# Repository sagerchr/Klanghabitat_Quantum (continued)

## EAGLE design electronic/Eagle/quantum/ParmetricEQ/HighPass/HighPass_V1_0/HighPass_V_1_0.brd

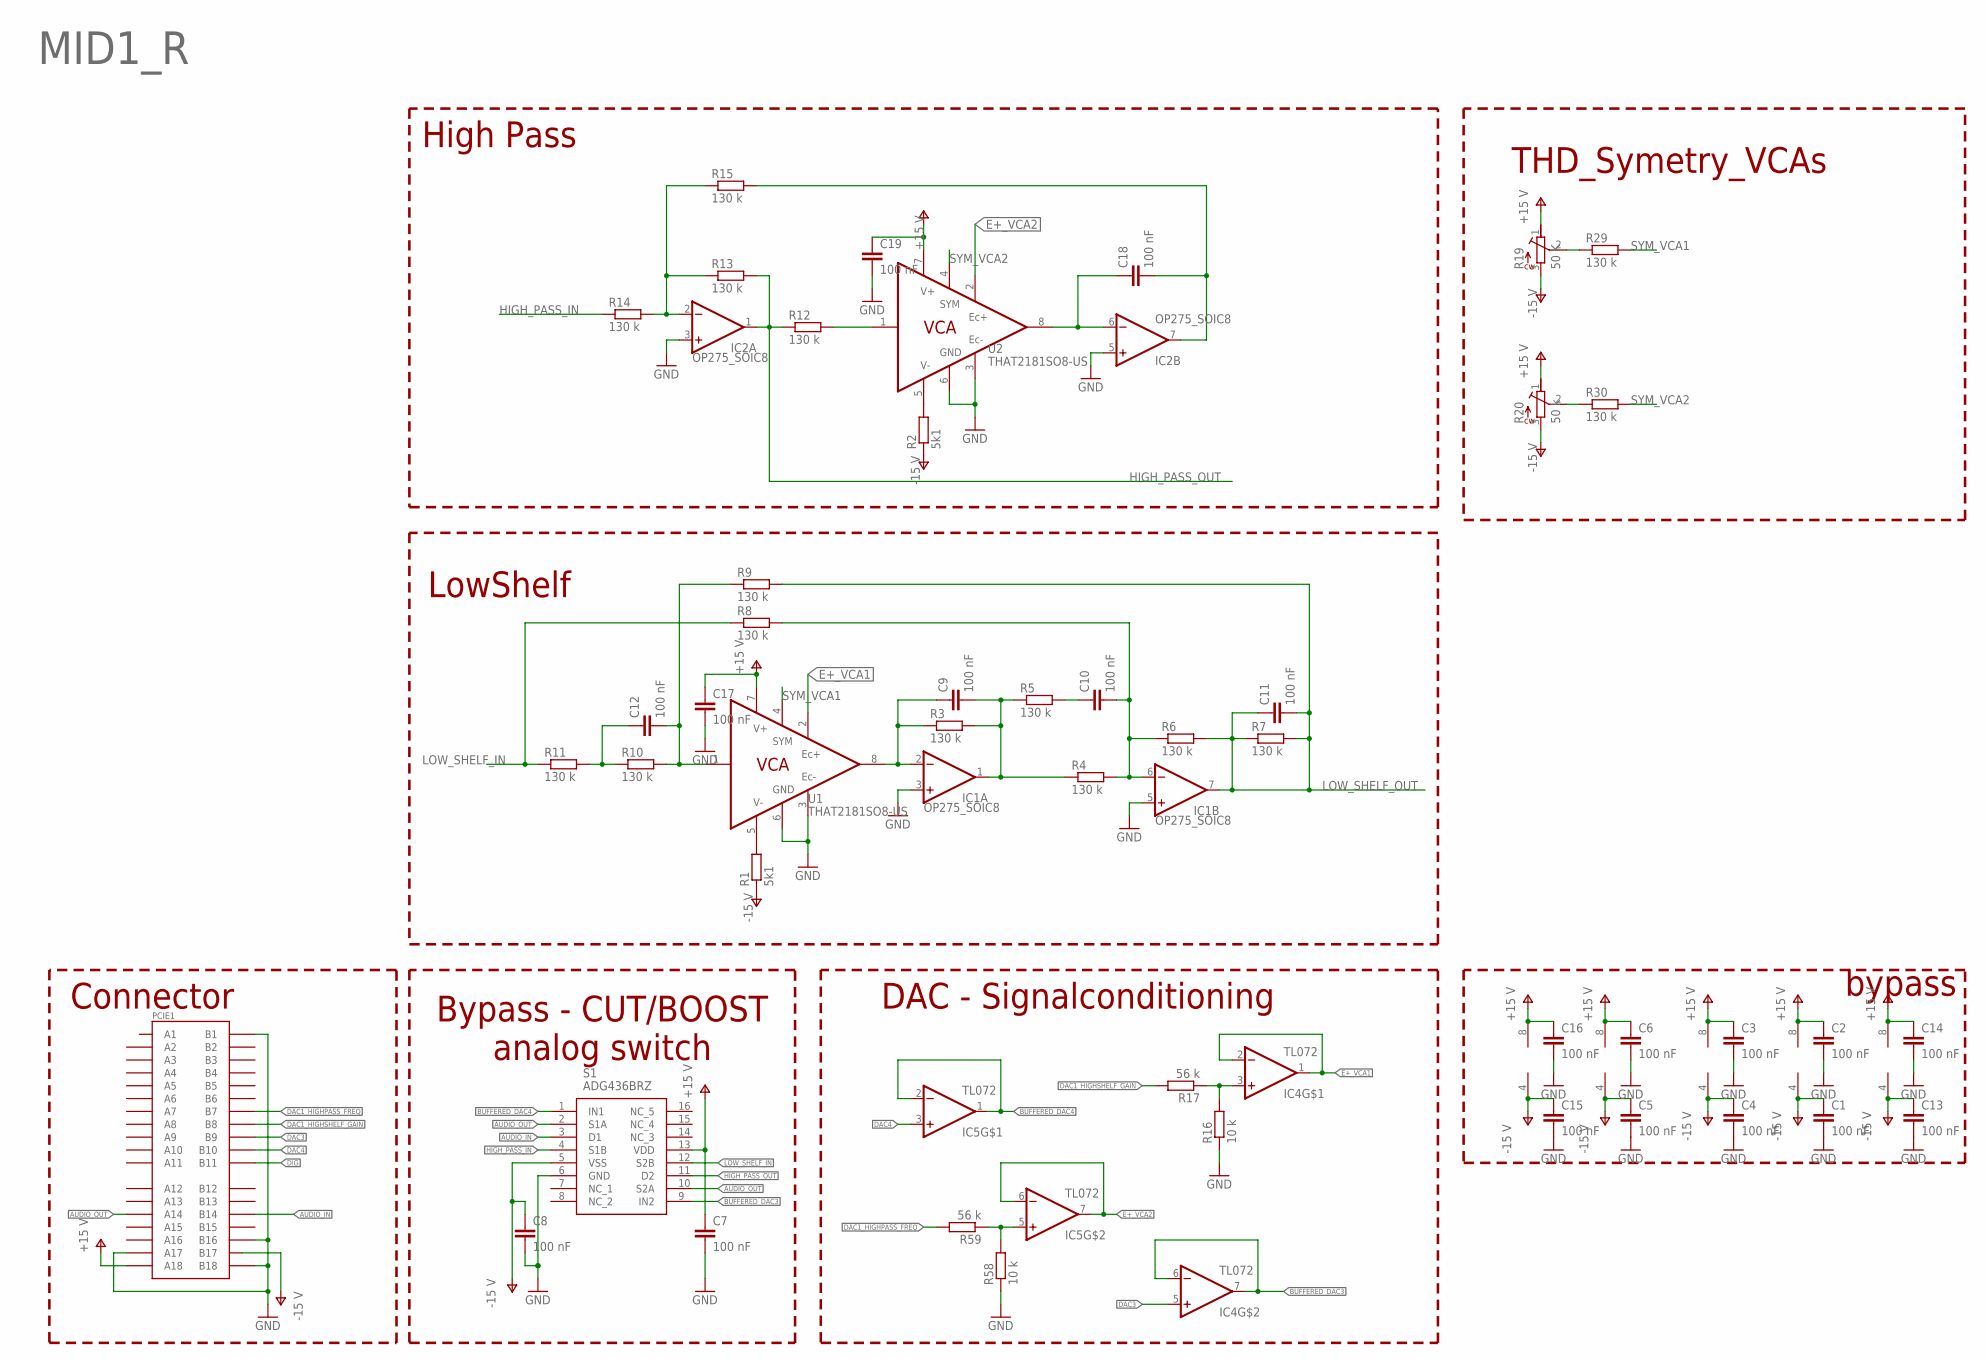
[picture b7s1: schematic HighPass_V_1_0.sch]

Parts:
C1, C2, C3, C4, C5, C6, C7, C8, C9, C10, C11, C12, C13, C14, C15, C16, C17, C18, C19: 100 nF; C0603
IC1, IC2, IC3: OP275_SOIC8; SOIC8
IC4, IC5: TL072; SOIC8
PCIE1: PCIE-36-EDGE
R1, R2: 5k1; R0603
R3, R4, R5, R6, R7, R8, R9, R10, R11, R12, R13, R14, R15, R29, R30: 130 k; R0603
R16, R58: 10 k; R0603
R17, R59: 56 k; R0603
R19: 50 K; TC33X2503G
R20: 50 k; TC33X2503G
S1: ADG436BRZ; SOIC127P600X175-16N
U1, U2: THAT2181SO8-US; SO08

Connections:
AUDIO_IN: PCIE1.B14, S1.3 (D1)
AUDIO_OUT: PCIE1.A14, S1.2 (S1A), S1.10 (S2A)
BUFFERED_DAC3: IC4.6 (-IN), IC4.7 (OUT), S1.9 (IN2)
BUFFERED_DAC4: IC5.1 (OUT), IC5.2 (-IN), S1.1 (IN1)
DAC1_HIGHPASS_FREQ: PCIE1.B7, R59.2
DAC1_HIGHSHELF_GAIN: PCIE1.B8, R17.2
DAC3: IC4.5 (+IN), PCIE1.B9
DAC4: IC5.3 (+IN), PCIE1.B10
DIG: PCIE1.B11
E+_VCA1: IC4.1 (OUT), IC4.2 (-IN), U1.2 (EC+)
E+_VCA2: IC5.6 (-IN), IC5.7 (OUT), U2.2 (EC+)
GND: C1.2, C2.2, C3.2, C4.2, C5.2, C6.2, C7.2, C8.2, C13.2, C14.2, C15.2, C16.2, C17.2, C19.2, IC1.3 (+IN), IC1.5 (+IN), IC2.3 (+IN), IC2.5 (+IN), PCIE1.A17, PCIE1.B1, PCIE1.B16, PCIE1.B18, R16.1, R58.1, S1.6 (GND), U1.3 (EC-), U1.6 (GND), U2.3 (EC-), U2.6 (GND)
HIGH_PASS_IN: R14.1, S1.4 (S1B)
HIGH_PASS_OUT: IC2.1 (OUT), R12.1, R13.2, S1.11 (D2)
LOW_SHELF_IN: R8.1, R11.1, S1.12 (S2B)
LOW_SHELF_OUT: C11.1, C11.2, IC1.7 (OUT), R6.2, R7.1, R7.2, R9.2
unnamed: R1.2, U1.5 (V-)
unnamed: R2.2, U2.5 (V-)
unnamed: C9.1, IC1.2 (-IN), R3.1, U1.8 (OUT)
unnamed: C10.2, IC1.6 (-IN), R4.2, R6.1, R8.2
unnamed: C9.2, IC1.1 (OUT), R3.2, R4.1, R5.1
unnamed: C10.1, R5.2
unnamed: R12.2, U2.1 (IN)
unnamed: C12.2, R9.1, R10.2, U1.1 (IN)
unnamed: IC4.3 (+IN), R16.2, R17.1
unnamed: C12.1, R10.1, R11.2
unnamed: IC2.2 (-IN), R13.1, R14.2, R15.1
unnamed: C18.2, IC2.7 (OUT), R15.2
unnamed: C18.1, IC2.6 (-IN), U2.8 (OUT)
unnamed: R19.2, R29.1
unnamed: R20.2, R30.1
unnamed: IC5.5 (+IN), R58.2, R59.1
SYM_VCA1: R29.2, U1.4 (SYM)
SYM_VCA2: R30.2, U2.4 (SYM)
V+: C2.1, C3.1, C6.1, C7.1, C14.1, C16.1, C17.1, C19.1, IC1.8 (V+), IC2.8 (V+), IC3.8 (V+), IC4.8 (V+), IC5.8 (V+), PCIE1.A18, R19.1 (3), R20.1 (3), S1.13 (VDD), U1.7 (V+), U2.7 (V+)
V-: C1.1, C4.1, C5.1, C8.1, C13.1, C15.1, IC1.4 (V-), IC2.4 (V-), IC3.4 (V-), IC4.4 (V-), IC5.4 (V-), PCIE1.B17, R1.1, R2.1, R19.3 (1), R20.3 (1), S1.5 (VSS)

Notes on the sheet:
DAC - Signalconditioning
MID1_R
LowShelf
High Pass
bypass
Bypass - CUT/BOOST analog switch
THD_Symetry_VCAs
Connector

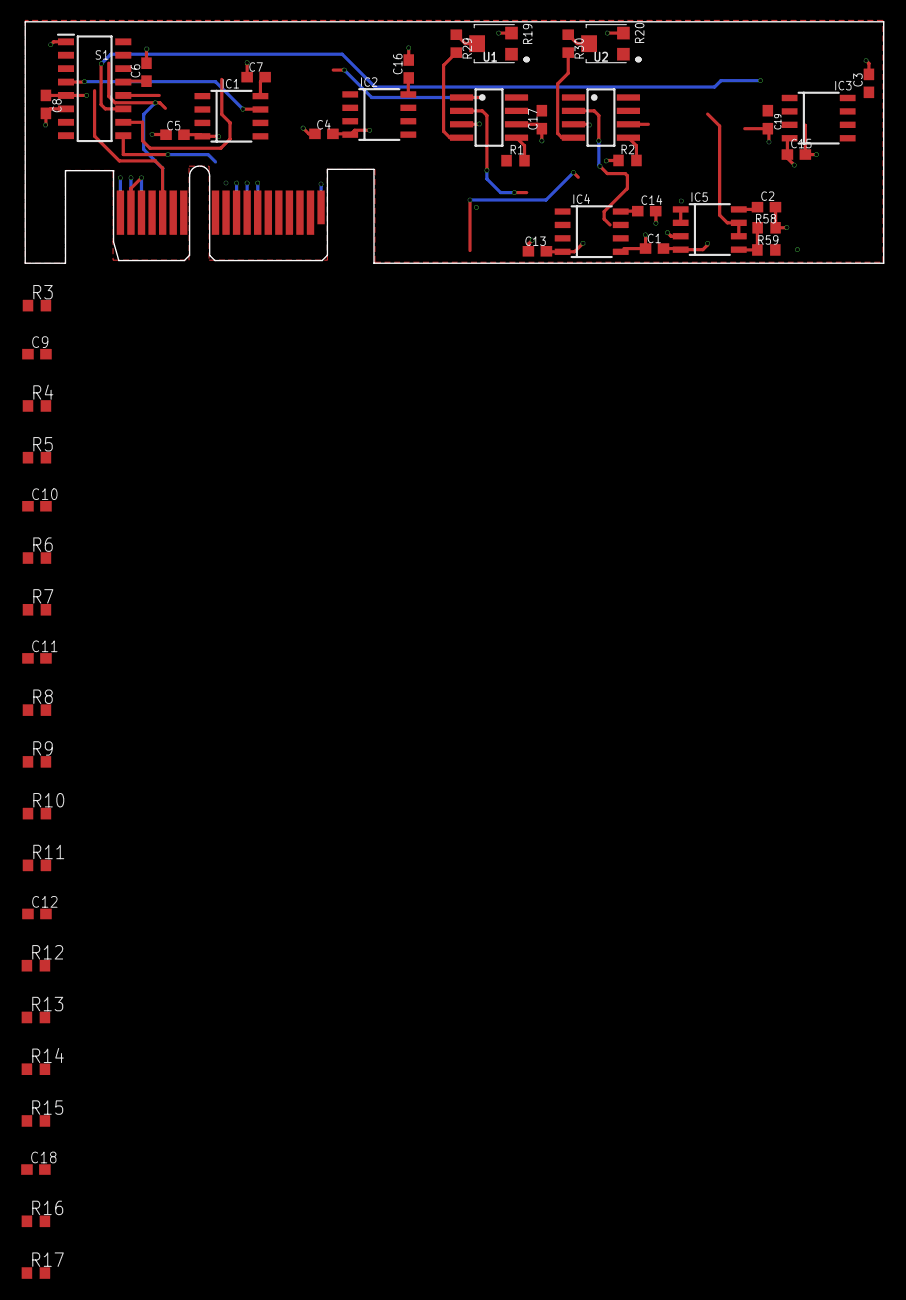
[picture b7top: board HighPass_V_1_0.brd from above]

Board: 4 copper layers, 81.3 x 22.9 mm, 51 parts (1 on the bottom side), 35 nets.

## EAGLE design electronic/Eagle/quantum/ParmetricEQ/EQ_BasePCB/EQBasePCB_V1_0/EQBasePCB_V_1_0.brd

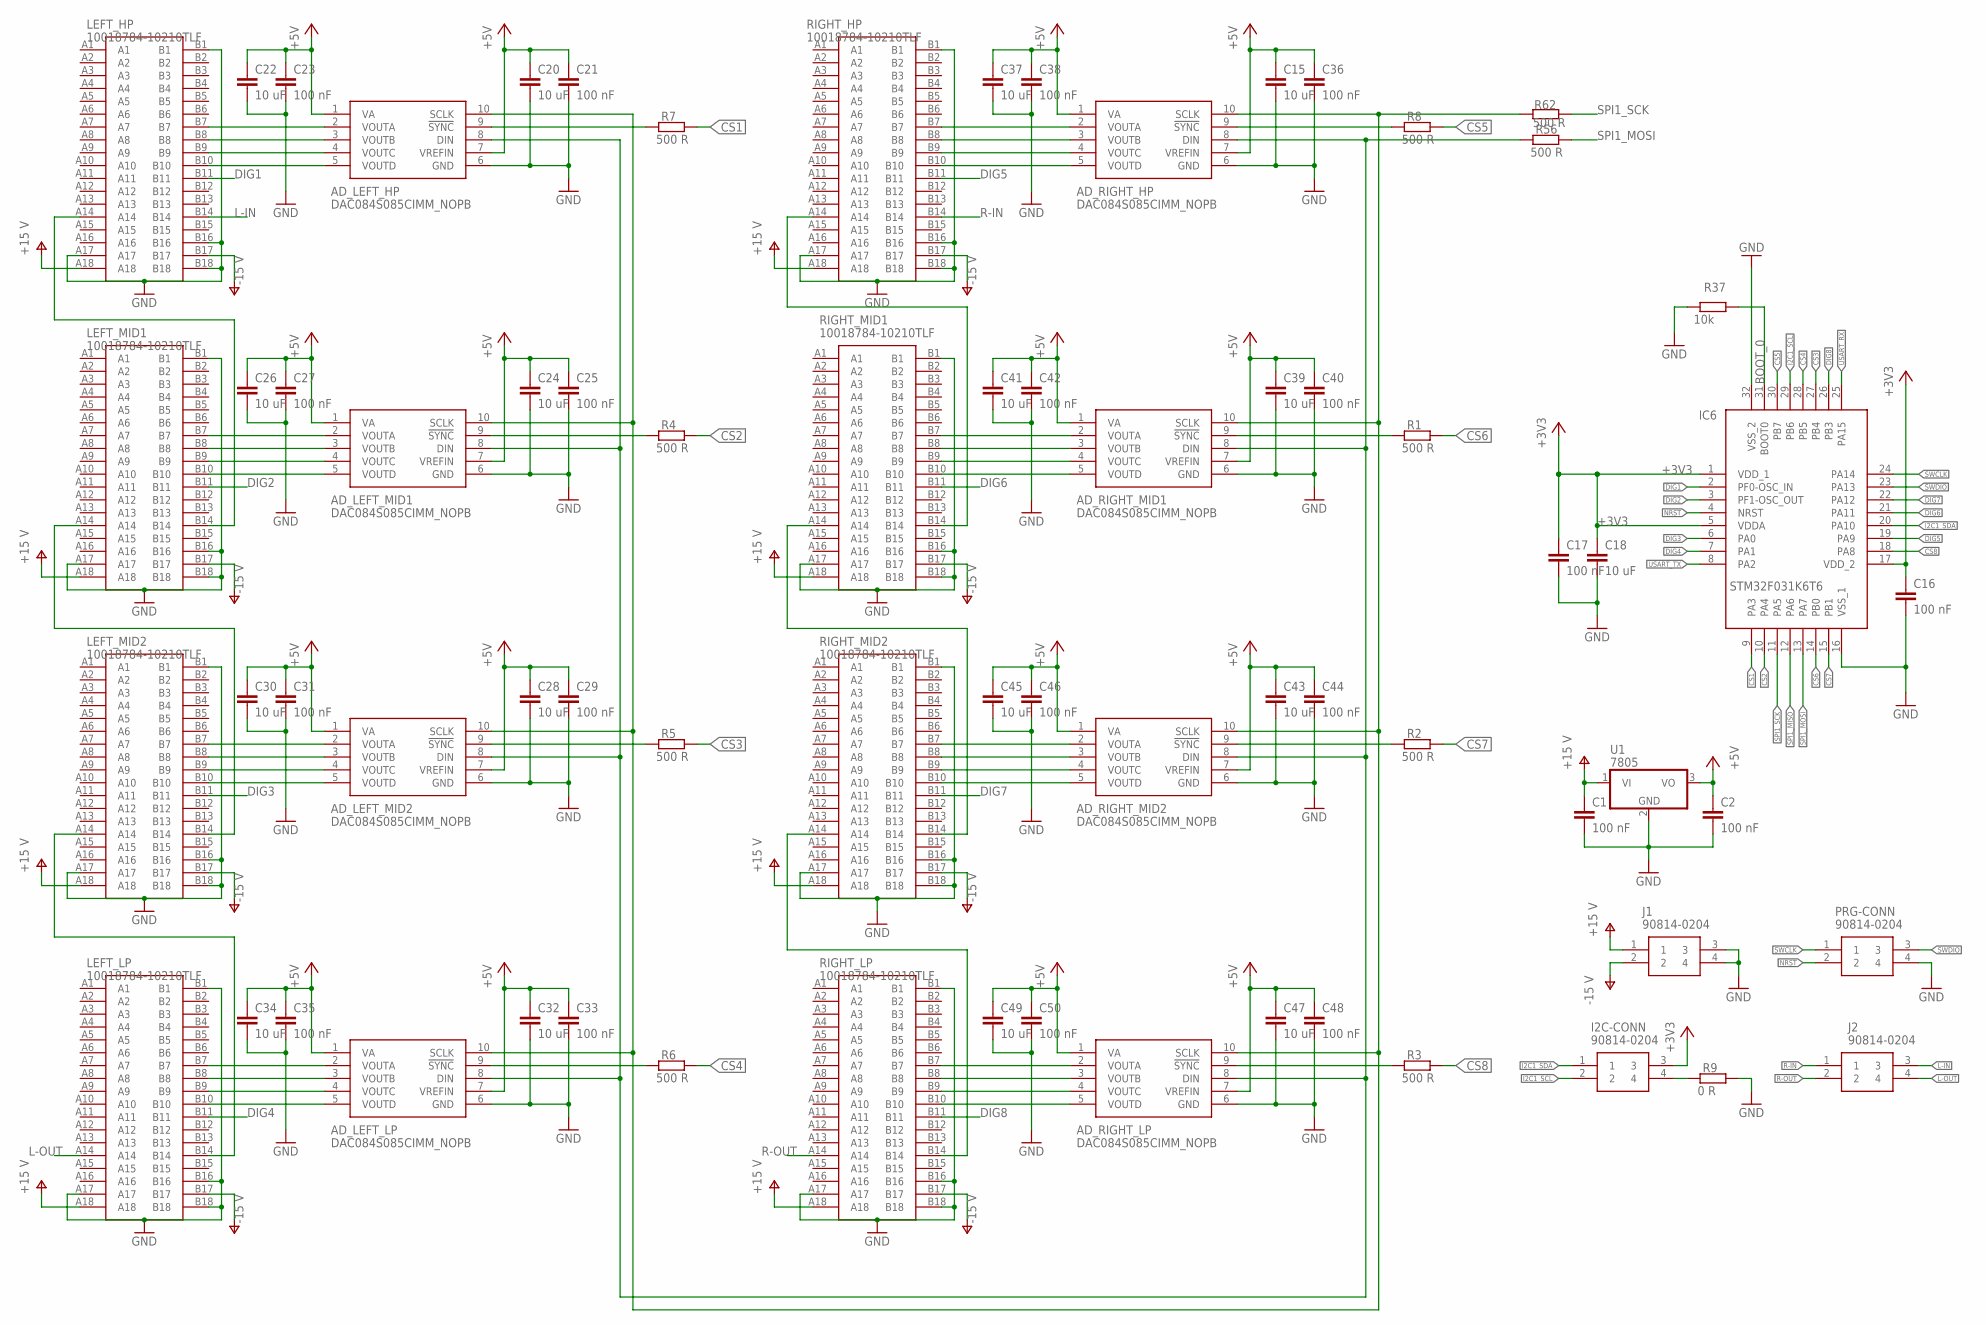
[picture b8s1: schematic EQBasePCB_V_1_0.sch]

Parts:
AD_LEFT_HP: DAC084S085CIMM_NOPB; SOP50P490X110-10N
AD_LEFT_LP: DAC084S085CIMM_NOPB; SOP50P490X110-10N
AD_LEFT_MID1, AD_LEFT_MID2: DAC084S085CIMM_NOPB; SOP50P490X110-10N
AD_RIGHT_HP: DAC084S085CIMM_NOPB; SOP50P490X110-10N
AD_RIGHT_LP: DAC084S085CIMM_NOPB; SOP50P490X110-10N
AD_RIGHT_MID1, AD_RIGHT_MID2: DAC084S085CIMM_NOPB; SOP50P490X110-10N
C1, C2, C16, C17, C21, C23, C25, C27, C29, C31, C33, C35, C36, C38, C40, C42, C44, C46, C48, C50: 100 nF; C0603
C15, C18, C20, C22, C24, C26, C28, C30, C32, C34, C37, C39, C41, C43, C45, C47, C49: 10 uF; C1206
I2C-CONN: 90814-0204; MOLEX_90814-0204
IC6: STM32F031K6T6; QFP80P900X900X160-32N
J1, J2: 90814-0204; MOLEX_90814-0204
LEFT_HP: 10018784-10210TLF; 1001878410210TLF
LEFT_LP: 10018784-10210TLF; 1001878410210TLF
LEFT_MID1, LEFT_MID2: 10018784-10210TLF; 1001878410210TLF
PRG-CONN: 90814-0204; MOLEX_90814-0204
R1, R2, R3, R4, R5, R6, R7, R8, R56, R62: 500 R; R0603
R9: 0 R; R0603
R37: 10k; R0603
RIGHT_HP: 10018784-10210TLF; 1001878410210TLF
RIGHT_LP: 10018784-10210TLF; 1001878410210TLF
RIGHT_MID1, RIGHT_MID2: 10018784-10210TLF; 1001878410210TLF
U1: 7805; TO252

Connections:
+3V3: C16.1, C17.1, C18.1, I2C-CONN.3, IC6.1 (VDD_1), IC6.5 (VDDA), IC6.17 (VDD_2)
+5V: AD_LEFT_HP.1 (VA), AD_LEFT_HP.7 (VREFIN), AD_LEFT_LP.1 (VA), AD_LEFT_LP.7 (VREFIN), AD_LEFT_MID1.1 (VA), AD_LEFT_MID1.7 (VREFIN), AD_LEFT_MID2.1 (VA), AD_LEFT_MID2.7 (VREFIN), AD_RIGHT_HP.1 (VA), AD_RIGHT_HP.7 (VREFIN), AD_RIGHT_LP.1 (VA), AD_RIGHT_LP.7 (VREFIN), AD_RIGHT_MID1.1 (VA), AD_RIGHT_MID1.7 (VREFIN), AD_RIGHT_MID2.1 (VA), AD_RIGHT_MID2.7 (VREFIN), C2.1, C15.1, C20.1, C21.1, C22.1, C23.1, C24.1, C25.1, C26.1, C27.1, C28.1, C29.1, C30.1, C31.1, C32.1, C33.1, C34.1, C35.1, C36.1, C37.1, C38.1, C39.1, C40.1, C41.1, C42.1, C43.1, C44.1, C45.1, C46.1, C47.1, C48.1, C49.1, C50.1, U1.3 (VO)
BOOT_0: IC6.31 (BOOT0), R37.2
CS1: IC6.9 (PA3), R7.2
CS2: IC6.10 (PA4), R4.2
CS3: IC6.27 (PB4), R5.2
CS4: IC6.28 (PB5), R6.2
CS5: IC6.30 (PB7), R8.2
CS6: IC6.14 (PB0), R1.2
CS7: IC6.15 (PB1), R2.2
CS8: IC6.18 (PA8), R3.2
DIG1: IC6.2 (PF0-OSC_IN), LEFT_HP.B11
DIG2: IC6.3 (PF1-OSC_OUT), LEFT_MID1.B11
DIG3: IC6.6 (PA0), LEFT_MID2.B11
DIG4: IC6.7 (PA1), LEFT_LP.B11
DIG5: IC6.19 (PA9), RIGHT_HP.B11
DIG6: IC6.21 (PA11), RIGHT_MID1.B11
DIG7: IC6.22 (PA12), RIGHT_MID2.B11
DIG8: IC6.26 (PB3), RIGHT_LP.B11
GND: AD_LEFT_HP.6 (GND), AD_LEFT_LP.6 (GND), AD_LEFT_MID1.6 (GND), AD_LEFT_MID2.6 (GND), AD_RIGHT_HP.6 (GND), AD_RIGHT_LP.6 (GND), AD_RIGHT_MID1.6 (GND), AD_RIGHT_MID2.6 (GND), C1.2, C2.2, C15.2, C16.2, C17.2, C18.2, C20.2, C21.2, C22.2, C23.2, C24.2, C25.2, C26.2, C27.2, C28.2, C29.2, C30.2, C31.2, C32.2, C33.2, C34.2, C35.2, C36.2, C37.2, C38.2, C39.2, C40.2, C41.2, C42.2, C43.2, C44.2, C45.2, C46.2, C47.2, C48.2, C49.2, C50.2, IC6.16 (VSS_1), IC6.32 (VSS_2), J1.3, J1.4, LEFT_HP.A17, LEFT_HP.B1, LEFT_HP.B16, LEFT_HP.B18, LEFT_LP.A17, LEFT_LP.B1, LEFT_LP.B16, LEFT_LP.B18, LEFT_MID1.A17, LEFT_MID1.B1, LEFT_MID1.B16, LEFT_MID1.B18, LEFT_MID2.A17, LEFT_MID2.B1, LEFT_MID2.B16, LEFT_MID2.B18, PRG-CONN.4, R9.2, R37.1, RIGHT_HP.A17, RIGHT_HP.B1, RIGHT_HP.B16, RIGHT_HP.B18, RIGHT_LP.A17, RIGHT_LP.B1, RIGHT_LP.B16, RIGHT_LP.B18, RIGHT_MID1.A17, RIGHT_MID1.B1, RIGHT_MID1.B16, RIGHT_MID1.B18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
I2C1_SCL: I2C-CONN.2, IC6.29 (PB6)
I2C1_SDA: I2C-CONN.1, IC6.20 (PA10)
L-IN: J2.3, LEFT_HP.B14
L-OUT: J2.4, LEFT_LP.A14
unnamed: AD_RIGHT_MID1.9 (!SYNC), R1.1
unnamed: AD_LEFT_MID1.5 (VOUTD), LEFT_MID1.B10
unnamed: I2C-CONN.4, R9.1
unnamed: LEFT_HP.A14, LEFT_MID1.B14
unnamed: LEFT_MID1.A14, LEFT_MID2.B14
unnamed: LEFT_LP.B14, LEFT_MID2.A14
unnamed: RIGHT_HP.A14, RIGHT_MID1.B14
unnamed: RIGHT_MID1.A14, RIGHT_MID2.B14
unnamed: RIGHT_LP.B14, RIGHT_MID2.A14
unnamed: AD_LEFT_HP.8 (DIN), AD_LEFT_LP.8 (DIN), AD_LEFT_MID1.8 (DIN), AD_LEFT_MID2.8 (DIN), AD_RIGHT_HP.8 (DIN), AD_RIGHT_LP.8 (DIN), AD_RIGHT_MID1.8 (DIN), AD_RIGHT_MID2.8 (DIN), R56.1
unnamed: AD_LEFT_HP.9 (!SYNC), R7.1
unnamed: AD_LEFT_HP.10 (SCLK), AD_LEFT_LP.10 (SCLK), AD_LEFT_MID1.10 (SCLK), AD_LEFT_MID2.10 (SCLK), AD_RIGHT_HP.10 (SCLK), AD_RIGHT_LP.10 (SCLK), AD_RIGHT_MID1.10 (SCLK), AD_RIGHT_MID2.10 (SCLK), R62.1
unnamed: AD_LEFT_HP.2 (VOUTA), LEFT_HP.B7
unnamed: AD_LEFT_HP.3 (VOUTB), LEFT_HP.B8
unnamed: AD_LEFT_HP.4 (VOUTC), LEFT_HP.B9
unnamed: AD_LEFT_HP.5 (VOUTD), LEFT_HP.B10
unnamed: AD_LEFT_MID1.9 (!SYNC), R4.1
unnamed: AD_LEFT_MID1.2 (VOUTA), LEFT_MID1.B7
unnamed: AD_LEFT_MID1.3 (VOUTB), LEFT_MID1.B8
unnamed: AD_LEFT_MID1.4 (VOUTC), LEFT_MID1.B9
unnamed: AD_LEFT_MID2.9 (!SYNC), R5.1
unnamed: AD_LEFT_MID2.2 (VOUTA), LEFT_MID2.B7
unnamed: AD_LEFT_MID2.3 (VOUTB), LEFT_MID2.B8
unnamed: AD_LEFT_MID2.4 (VOUTC), LEFT_MID2.B9
unnamed: AD_LEFT_MID2.5 (VOUTD), LEFT_MID2.B10
unnamed: AD_LEFT_LP.9 (!SYNC), R6.1
unnamed: AD_LEFT_LP.2 (VOUTA), LEFT_LP.B7
unnamed: AD_LEFT_LP.3 (VOUTB), LEFT_LP.B8
unnamed: AD_LEFT_LP.4 (VOUTC), LEFT_LP.B9
unnamed: AD_LEFT_LP.5 (VOUTD), LEFT_LP.B10
unnamed: AD_RIGHT_HP.9 (!SYNC), R8.1
unnamed: AD_RIGHT_HP.2 (VOUTA), RIGHT_HP.B7
unnamed: AD_RIGHT_HP.3 (VOUTB), RIGHT_HP.B8
unnamed: AD_RIGHT_HP.4 (VOUTC), RIGHT_HP.B9
unnamed: AD_RIGHT_HP.5 (VOUTD), RIGHT_HP.B10
unnamed: AD_RIGHT_MID1.2 (VOUTA), RIGHT_MID1.B7
unnamed: AD_RIGHT_MID1.3 (VOUTB), RIGHT_MID1.B8
unnamed: AD_RIGHT_MID1.4 (VOUTC), RIGHT_MID1.B9
unnamed: AD_RIGHT_MID1.5 (VOUTD), RIGHT_MID1.B10
unnamed: AD_RIGHT_MID2.9 (!SYNC), R2.1
unnamed: AD_RIGHT_MID2.2 (VOUTA), RIGHT_MID2.B7
unnamed: AD_RIGHT_MID2.3 (VOUTB), RIGHT_MID2.B8
unnamed: AD_RIGHT_MID2.4 (VOUTC), RIGHT_MID2.B9
unnamed: AD_RIGHT_MID2.5 (VOUTD), RIGHT_MID2.B10
unnamed: AD_RIGHT_LP.9 (!SYNC), R3.1
unnamed: AD_RIGHT_LP.2 (VOUTA), RIGHT_LP.B7
unnamed: AD_RIGHT_LP.3 (VOUTB), RIGHT_LP.B8
unnamed: AD_RIGHT_LP.4 (VOUTC), RIGHT_LP.B9
unnamed: AD_RIGHT_LP.5 (VOUTD), RIGHT_LP.B10
NRST: IC6.4 (NRST), PRG-CONN.2
R-IN: J2.1, RIGHT_HP.B14
R-OUT: J2.2, RIGHT_LP.A14
SPI1_MISO: IC6.12 (PA6)
SPI1_MOSI: IC6.13 (PA7), R56.2
SPI1_SCK: IC6.11 (PA5), R62.2
SWCLK: IC6.24 (PA14), PRG-CONN.1
SWDIO: IC6.23 (PA13), PRG-CONN.3
USART_RX: IC6.25 (PA15)
USART_TX: IC6.8 (PA2)
V+: C1.1, J1.1, LEFT_HP.A18, LEFT_LP.A18, LEFT_MID1.A18, LEFT_MID2.A18, RIGHT_HP.A18, RIGHT_LP.A18, RIGHT_MID1.A18, RIGHT_MID2.A18, U1.1 (VI)
V-: J1.2, LEFT_HP.B17, LEFT_LP.B17, LEFT_MID1.B17, LEFT_MID2.B17, RIGHT_HP.B17, RIGHT_LP.B17, RIGHT_MID1.B17, RIGHT_MID2.B17

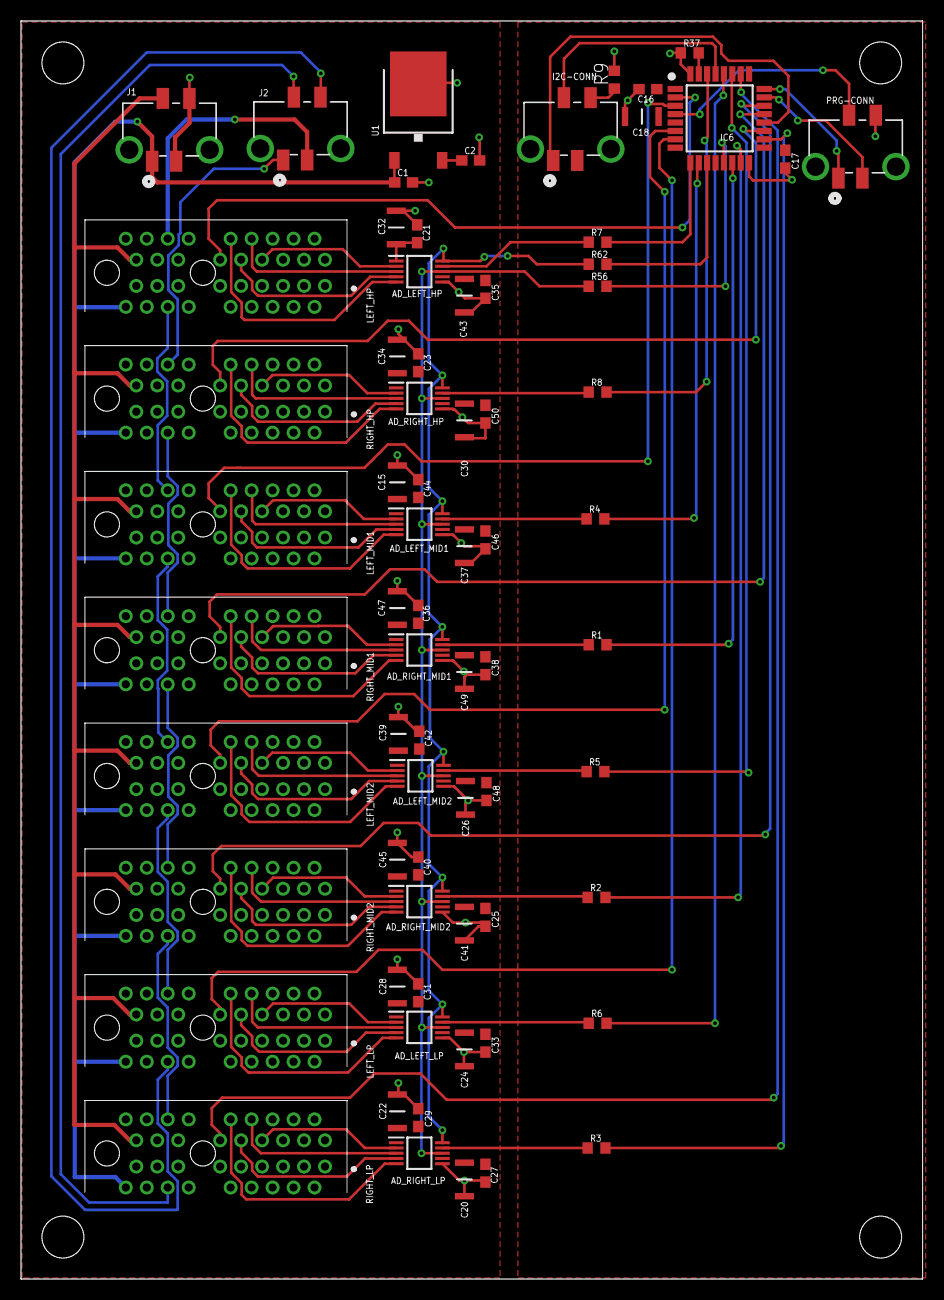
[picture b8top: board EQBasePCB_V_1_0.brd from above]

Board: 2 copper layers, 86.0 x 120.0 mm, 71 parts (0 on the bottom side), 82 nets.

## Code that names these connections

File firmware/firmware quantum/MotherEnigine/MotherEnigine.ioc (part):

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Mcu.Name=STM32F767ZITx
Mcu.Package=LQFP144
Mcu.UserName=STM32F767ZITx
PA1.GPIOParameters=GPIO_Label
PA1.GPIO_Label=RMII_REF_CLK [LAN8742A-CZ-TR_REFCLK0]
PA1.Mode=RMII
PA1.Signal=ETH_REF_CLK
PA10.GPIOParameters=GPIO_Label
PA10.GPIO_Label=USB_ID
PA10.Signal=USB_OTG_FS_ID
PA11.GPIOParameters=GPIO_Label
PA11.GPIO_Label=USB_DM
PA11.Signal=USB_OTG_FS_DM
PA12.GPIOParameters=GPIO_Label
PA12.GPIO_Label=USB_DP
PA12.Signal=USB_OTG_FS_DP
PA13.GPIOParameters=GPIO_Label
PA13.GPIO_Label=TMS
PA13.Mode=Serial_Wire
PA13.Signal=SYS_JTMS-SWDIO
PA14.GPIOParameters=GPIO_Label
PA14.GPIO_Label=TCK
PA14.Mode=Serial_Wire
PA14.Signal=SYS_JTCK-SWCLK
PA2.GPIOParameters=GPIO_Label
PA2.GPIO_Label=RMII_MDIO [LAN8742A-CZ-TR_MDIO]
PA2.Mode=RMII
PA2.Signal=ETH_MDIO
PA4.Signal=COMP_DAC1_group
PA5.Signal=COMP_DAC2_group
PA7.GPIOParameters=GPIO_Label
PA7.GPIO_Label=RMII_CRS_DV [LAN8742A-CZ-TR_CRS_DV]
PA7.Mode=RMII
PA7.Signal=ETH_CRS_DV
PA8.GPIOParameters=GPIO_Label
PA8.GPIO_Label=USB_SOF [TP1]
PA8.Signal=USB_OTG_FS_SOF
PA9.GPIOParameters=GPIO_Label
PA9.GPIO_Label=USB_VBUS
PA9.Signal=USB_OTG_FS_VBUS
PB0.GPIOParameters=GPIO_Label
PB0.GPIO_Label=LD1 [Green]
PB0.Signal=GPIO_Output
PB10.Mode=TX_Only_Simplex_Unidirect_Master
PB10.Signal=SPI2_SCK
PB12.GPIOParameters=GPIO_Label
PB12.GPIO_Label=PB12
PB12.Signal=GPIO_Output
PB13.GPIOParameters=GPIO_Label
PB13.GPIO_Label=RMII_TXD1 [LAN8742A-CZ-TR_TXD1]
PB13.Mode=RMII
PB13.Signal=ETH_TXD1
PB14.GPIOParameters=GPIO_Label
PB14.GPIO_Label=LD3 [Red]
PB14.Signal=GPIO_Output
PB3.GPIOParameters=GPIO_Label
PB3.GPIO_Label=SWO
PB3.Signal=SYS_JTDO-SWO
PB4.GPIOParameters=GPIO_Label
PB4.GPIO_Label=CS_DAC1
PB4.Signal=GPIO_Output
PB5.GPIOParameters=GPIO_Label
PB5.GPIO_Label=CS_POTI
PB5.Signal=GPIO_Output
PB7.GPIOParameters=GPIO_Label
PB7.GPIO_Label=LD2 [Blue]
PB7.Signal=GPIO_Output
PC1.GPIOParameters=GPIO_Label
PC1.GPIO_Label=RMII_MDC [LAN8742A-CZ-TR_MDC]
PC1.Mode=RMII
PC1.Signal=ETH_MDC
PC10.GPIOParameters=GPIO_Label
PC10.GPIO_Label=OS2
PC10.Signal=GPIO_Output
PC11.GPIOParameters=GPIO_Label
PC11.GPIO_Label=RANGE
PC11.Signal=GPIO_Output
PC12.GPIOParameters=GPIO_Label
PC12.GPIO_Label=CV_A_B
PC12.Signal=GPIO_Output
PC13.GPIOParameters=GPIO_Label
PC13.GPIO_Label=USER_Btn [B1]
PC13.Signal=GPXTI13
PC14/OSC32_IN.Mode=LSE-External-Oscillator
PC14/OSC32_IN.Signal=RCC_OSC32_IN
PC15/OSC32_OUT.Mode=LSE-External-Oscillator
PC15/OSC32_OUT.Signal=RCC_OSC32_OUT
PC3.Mode=TX_Only_Simplex_Unidirect_Master
PC3.Signal=SPI2_MOSI
PC4.GPIOParameters=GPIO_Label
PC4.GPIO_Label=RMII_RXD0 [LAN8742A-CZ-TR_RXD0]
PC4.Mode=RMII
PC4.Signal=ETH_RXD0
PC5.GPIOParameters=GPIO_Label
PC5.GPIO_Label=RMII_RXD1 [LAN8742A-CZ-TR_RXD1]
PC5.Mode=RMII
PC5.Signal=ETH_RXD1
PC6.Mode=Asynchronous
PC6.Signal=USART6_TX
PC7.Mode=Asynchronous
PC7.Signal=USART6_RX
PC8.GPIOParameters=GPIO_Label
PC8.GPIO_Label=OS0
PC8.Signal=GPIO_Output
PC9.GPIOParameters=GPIO_Label
PC9.GPIO_Label=OS1
PC9.Signal=GPIO_Output
PD1.GPIOParameters=GPIO_Label
PD1.GPIO_Label=DEBUG2
PD1.Signal=GPIO_Output
PD10.GPIOParameters=GPIO_Label
PD10.GPIO_Label=MUTE_POTI
PD10.Signal=GPIO_Output
PD11.GPIOParameters=GPIO_Label
PD11.GPIO_Label=ZCEN
PD11.Signal=GPIO_Output
PD2.GPIOParameters=GPIO_Label
PD2.GPIO_Label=RD
PD2.Signal=GPIO_Output
PD6.GPIOParameters=GPIO_Label
PD6.GPIO_Label=FRST
PD6.Signal=GPIO_Input
PD7.GPIOParameters=GPIO_Label
PD7.GPIO_Label=CS
PD7.Signal=GPIO_Output
PD8.GPIOParameters=GPIO_Label
PD8.GPIO_Label=STLK_RX [STM32F103CBT6_PA3]
PD8.Mode=Asynchronous
PD8.Signal=USART3_TX
PD9.GPIOParameters=GPIO_Label
PD9.GPIO_Label=STLK_TX [STM32F103CBT6_PA2]
PD9.Mode=Asynchronous
PD9.Signal=USART3_RX
PE0.GPIOParameters=GPIO_Label
PE0.GPIO_Label=DB0
PE0.Signal=GPIO_Input
PE1.GPIOParameters=GPIO_Label
PE1.GPIO_Label=DB1
PE1.Signal=GPIO_Input
PE10.GPIOParameters=GPIO_Label
PE10.GPIO_Label=DB10
PE10.Signal=GPIO_Input
PE11.GPIOParameters=GPIO_Label
PE11.GPIO_Label=DB11
PE11.Signal=GPIO_Input
PE12.GPIOParameters=GPIO_Label
PE12.GPIO_Label=DB12
PE12.Signal=GPIO_Input
PE13.GPIOParameters=GPIO_Label
PE13.GPIO_Label=DB13
PE13.Signal=GPIO_Input
PE14.GPIOParameters=GPIO_Label
PE14.GPIO_Label=DB14
PE14.Signal=GPIO_Input
PE15.GPIOParameters=GPIO_Label
PE15.GPIO_Label=DB15
PE15.Signal=GPIO_Input
PE2.GPIOParameters=GPIO_Label
PE2.GPIO_Label=DB2
PE2.Signal=GPIO_Input
PE3.GPIOParameters=GPIO_Label
PE3.GPIO_Label=DB3
PE3.Signal=GPIO_Input
PE4.GPIOParameters=GPIO_Label
PE4.GPIO_Label=DB4
PE4.Signal=GPIO_Input
PE5.GPIOParameters=GPIO_Label
PE5.GPIO_Label=DB5
PE5.Signal=GPIO_Input
PE6.GPIOParameters=GPIO_Label
PE6.GPIO_Label=DB6
PE6.Signal=GPIO_Input
PE7.GPIOParameters=GPIO_Label
PE7.GPIO_Label=DB7
PE7.Signal=GPIO_Input
PE8.GPIOParameters=GPIO_Label
PE8.GPIO_Label=DB8
PE8.Signal=GPIO_Input
PE9.GPIOParameters=GPIO_Label
PE9.GPIO_Label=DB9
PE9.Signal=GPIO_Input
PF6.Signal=S_TIM10_CH1
PF9.GPIOParameters=GPIO_Label
PF9.GPIO_Label=DEBUG1
PF9.Signal=GPIO_Output
PG0.GPIOParameters=GPIO_Label
PG0.GPIO_Label=Relais2
PG0.Signal=GPIO_Output
PG1.GPIOParameters=GPIO_Label
PG1.GPIO_Label=Relais1
PG1.Signal=GPIO_Output
PG10.GPIOParameters=GPIO_Label
PG10.GPIO_Label=Relais4
PG10.Signal=GPIO_Output
PG11.GPIOParameters=GPIO_Label
PG11.GPIO_Label=RMII_TX_EN [LAN8742A-CZ-TR_TXEN]
PG11.Mode=RMII
PG11.Signal=ETH_TX_EN
PG12.GPIOParameters=GPIO_Label
PG12.GPIO_Label=Relais5
PG12.Signal=GPIO_Output
PG13.GPIOParameters=GPIO_Label
PG13.GPIO_Label=RMII_TXD0 [LAN8742A-CZ-TR_TXD0]
PG13.Mode=RMII
PG13.Signal=ETH_TXD0
PG15.GPIOParameters=GPIO_Label
PG15.GPIO_Label=Relais3
PG15.Signal=GPIO_Output
PG2.GPIOParameters=GPIO_Label
PG2.GPIO_Label=RESET
PG2.Signal=GPIO_Output
PG3.GPIOParameters=GPIO_Label
PG3.GPIO_Label=BUSY
PG3.Signal=GPIO_Input
PG6.GPIOParameters=GPIO_Label
PG6.GPIO_Label=USB_PowerSwitchOn [STMPS2151STR_EN]
PG6.Signal=GPIO_Output
PG7.GPIOParameters=GPIO_Label
PG7.GPIO_Label=USB_OverCurrent [STMPS2151STR_FAULT]
PG7.Signal=GPIO_Input
PG9.GPIOParameters=GPIO_Label
PG9.GPIO_Label=Relais6
PG9.Signal=GPIO_Output
PH0/OSC_IN.GPIOParameters=GPIO_Label
PH0/OSC_IN.GPIO_Label=MCO [STM32F103CBT6_PA8]
PH0/OSC_IN.Mode=HSE-External-Oscillator
PH0/OSC_IN.Signal=RCC_OSC_IN
PH1/OSC_OUT.Mode=HSE-External-Oscillator
PH1/OSC_OUT.Signal=RCC_OSC_OUT
RCC.HSE_VALUE=8000000
RCC.SYSCLKFreq_VALUE=216000000
RCC.SYSCLKSource=RCC_SYSCLKSOURCE_PLLCLK
RCC.SYSCLKSourceVirtual=RCC_SYSCLKSOURCE_PLLCLK
board=NUCLEO-F767ZI
boardIOC=true

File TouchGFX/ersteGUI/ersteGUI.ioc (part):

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Mcu.Name=STM32F769NIHx
Mcu.Package=TFBGA216
Mcu.UserName=STM32F769NIHx
PA0/WKUP.GPIOParameters=GPIO_Label
PA0/WKUP.GPIO_Label=B_USER [B1]
PA0/WKUP.Signal=GPXTI0
PA1.GPIOParameters=GPIO_Label
PA1.GPIO_Label=RMII_REF_CLK [LAN8742A-CZ-TR_REFCLK0]
PA1.Signal=ETH_REF_CLK
PA10.GPIOParameters=GPIO_Label
PA10.GPIO_Label=VCP_RX 
PA10.Mode=Asynchronous
PA10.Signal=USART1_RX
PA11.GPIOParameters=GPIO_Label
PA11.GPIO_Label=SPI2_NSS
PA11.Mode=NSS_Signal_Hard_Input
PA11.Signal=SPI2_NSS
PA12.GPIOParameters=GPIO_Speed,GPIO_PuPd,GPIO_Label,GPIO_Mode
PA12.GPIO_Label=ARD_D13/SCK
PA12.GPIO_Mode=GPIO_MODE_AF_PP
PA12.GPIO_PuPd=GPIO_NOPULL
PA12.GPIO_Speed=GPIO_SPEED_FREQ_LOW
PA12.Mode=Full_Duplex_Master
PA12.Signal=SPI2_SCK
PA13.GPIOParameters=GPIO_Label
PA13.GPIO_Label=SWDIO
PA13.Mode=Serial_Wire
PA13.Signal=SYS_JTMS-SWDIO
PA14.GPIOParameters=GPIO_Label
PA14.GPIO_Label=SWCLK
PA14.Mode=Serial_Wire
PA14.Signal=SYS_JTCK-SWCLK
PA15.GPIOParameters=GPIO_Label
PA15.GPIO_Label=CEC
PA15.Signal=CEC
PA2.GPIOParameters=GPIO_Label
PA2.GPIO_Label=RMII_MDIO [LAN8742A-CZ-TR_MDIO]
PA2.Signal=ETH_MDIO
PA3.GPIOParameters=GPIO_Label
PA3.GPIO_Label=ULPI_D0 [USB3320C-EZK_D0]
PA3.Signal=USB_OTG_HS_ULPI_D0
PA4.GPIOParameters=GPIO_Label
PA4.GPIO_Label=ARD_A1
PA4.Signal=ADCx_IN4
PA5.GPIOParameters=GPIO_Label
PA5.GPIO_Label=ULPI_CLK [USB3320C-EZK_CLKOUT]
PA5.Signal=USB_OTG_HS_ULPI_CK
PA6.GPIOParameters=GPIO_Label
PA6.GPIO_Label=ARD_A0
PA6.Signal=ADCx_IN6
PA7.GPIOParameters=GPIO_Label
PA7.GPIO_Label=RMII_CRS_DV [LAN8742A-CZ-TR_CRS_DV]
PA7.Signal=ETH_CRS_DV
PA8.GPIOParameters=GPIO_Label
PA8.GPIO_Label=CEC_CLK [TP2]
PA8.Mode=Clock-out-1
PA8.Signal=RCC_MCO_1
PA9.GPIOParameters=GPIO_Speed,GPIO_PuPd,GPIO_Label,GPIO_Mode
PA9.GPIO_Label=VCP_TX [STM32F103CBT6_PA3]
PA9.GPIO_Mode=GPIO_MODE_AF_PP
PA9.GPIO_PuPd=GPIO_NOPULL
PA9.GPIO_Speed=GPIO_SPEED_FREQ_LOW
PA9.Mode=Asynchronous
PA9.Signal=USART1_TX
PB0.GPIOParameters=GPIO_Label
PB0.GPIO_Label=ULPI_D1 [USB3320C-EZK_D1]
PB0.Signal=USB_OTG_HS_ULPI_D1
PB1.GPIOParameters=GPIO_Label
PB1.GPIO_Label=ULPI_D2 [USB3320C-EZK_D2]
PB1.Signal=USB_OTG_HS_ULPI_D2
PB10.GPIOParameters=GPIO_Label
PB10.GPIO_Label=ULPI_D3 [USB3320C-EZK_D3]
PB10.Signal=USB_OTG_HS_ULPI_D3
PB11.GPIOParameters=GPIO_Label
PB11.GPIO_Label=ULPI_D4 [USB3320C-EZK_D4]
PB11.Signal=USB_OTG_HS_ULPI_D4
PB12.GPIOParameters=GPIO_Label
PB12.GPIO_Label=ULPI_D5 [USB3320C-EZK_D5]
PB12.Signal=USB_OTG_HS_ULPI_D5
PB13.GPIOParameters=GPIO_Label
PB13.GPIO_Label=ULPI_D6 [USB3320C-EZK_D6]
PB13.Signal=USB_OTG_HS_ULPI_D6
PB14.GPIOParameters=GPIO_Speed,GPIO_PuPd,GPIO_Label,GPIO_Mode
PB14.GPIO_Label=ARDUINO MISO/D12
PB14.GPIO_Mode=GPIO_MODE_AF_PP
PB14.GPIO_PuPd=GPIO_NOPULL
PB14.GPIO_Speed=GPIO_SPEED_FREQ_LOW
PB14.Mode=Full_Duplex_Master
PB14.Signal=SPI2_MISO
PB15.GPIOParameters=GPIO_Speed,GPIO_PuPd,GPIO_Label,GPIO_Mode
PB15.GPIO_Label=ARDUINO MOSI/PWM/D11
PB15.GPIO_Mode=GPIO_MODE_AF_PP
PB15.GPIO_PuPd=GPIO_NOPULL
PB15.GPIO_Speed=GPIO_SPEED_FREQ_LOW
PB15.Mode=Full_Duplex_Master
PB15.Signal=SPI2_MOSI
PB2.Mode=Single Bank 1
PB2.Signal=QUADSPI_CLK
PB3.GPIOParameters=GPIO_Label
PB3.GPIO_Label=uSD_D2
PB3.Signal=SDMMC2_D2
PB4.GPIOParameters=GPIO_Label
PB4.GPIO_Label=uSD_D3
PB4.Signal=SDMMC2_D3
PB5.GPIOParameters=GPIO_Label
PB5.GPIO_Label=ULPI_D7 [USB3320C-EZK_D7]
PB5.Signal=USB_OTG_HS_ULPI_D7
PB6.GPIOParameters=GPIO_Label
PB6.GPIO_Label=QSPI_NCS [N25Q128A13EF840E_S]
PB6.Mode=Single Bank 1
PB6.Signal=QUADSPI_BK1_NCS
PB7.GPIOParameters=GPIO_Label
PB7.GPIO_Label=AUDIO_SDA [WM8994ECS/R_SDA]
PB7.Signal=I2C4_SDA
PB8.GPIOParameters=GPIO_Speed,GPIO_PuPd,GPIO_Label,GPIO_Mode
PB8.GPIO_Label=ARDUINO SCL/D15
PB8.GPIO_Mode=GPIO_MODE_AF_OD
PB8.GPIO_PuPd=GPIO_NOPULL
PB8.GPIO_Speed=GPIO_SPEED_FREQ_LOW
PB8.Signal=I2C1_SCL
PB9.GPIOParameters=GPIO_Speed,GPIO_PuPd,GPIO_Label,GPIO_Mode
PB9.GPIO_Label=ARDUINO SDA/D14
PB9.GPIO_Mode=GPIO_MODE_AF_OD
PB9.GPIO_PuPd=GPIO_NOPULL
PB9.GPIO_Speed=GPIO_SPEED_FREQ_LOW
PB9.Signal=I2C1_SDA
PC0.GPIOParameters=GPIO_Label
PC0.GPIO_Label=ULPI_STP [USB3320C-EZK_STP]
PC0.Signal=USB_OTG_HS_ULPI_STP
PC1.GPIOParameters=GPIO_Label
PC1.GPIO_Label=RMII_MDC [LAN8742A-CZ-TR_MDC]
PC1.Signal=ETH_MDC
PC10.GPIOParameters=GPIO_Label
PC10.GPIO_Label=QSPI_D1 [MT25QL512ABB1EW9_DQ1]
PC10.Mode=Single Bank 1
PC10.Signal=QUADSPI_BK1_IO1
PC11.GPIOParameters=GPIO_Label
PC11.GPIO_Label=DFSDM_DATIN5 [TP5]
PC11.Signal=S_DATAIN5DFSDM1
PC12.GPIOParameters=GPIO_Label
PC12.GPIO_Label=WIFI_RX
PC12.Signal=UART5_TX
PC13.Signal=RTC_OUT_ALARM
PC14/OSC32_IN.GPIOParameters=GPIO_Label
PC14/OSC32_IN.GPIO_Label=RCC_OSC32_IN
PC14/OSC32_IN.Mode=LSE-External-Oscillator
PC14/OSC32_IN.Signal=RCC_OSC32_IN
PC15/OSC32_OUT.GPIOParameters=GPIO_Label
PC15/OSC32_OUT.GPIO_Label=RCC_OSC32_OUT
PC15/OSC32_OUT.Mode=LSE-External-Oscillator
PC15/OSC32_OUT.Signal=RCC_OSC32_OUT
PC2.GPIOParameters=GPIO_Label
PC2.GPIO_Label=ARD_A2
PC2.Signal=ADCx_IN12
PC4.GPIOParameters=GPIO_Label
PC4.GPIO_Label=RMII_RXD0 [LAN8742A-CZ-TR_RXD0]
PC4.Signal=ETH_RXD0
PC5.GPIOParameters=GPIO_Label
PC5.GPIO_Label=RMII_RXD1 [LAN8742A-CZ-TR_RXD1]
PC5.Signal=ETH_RXD1
PC6.GPIOParameters=GPIO_Label
PC6.GPIO_Label=ARDUINO TX/D1
PC6.Signal=USART6_TX
PC7.GPIOParameters=GPIO_Label
PC7.GPIO_Label=ARD_D0/RX
PC7.Signal=USART6_RX
PC8.GPIOParameters=GPIO_Label
PC8.GPIO_Label=ARD_D5/PWM
PC8.Signal=S_TIM3_CH3
PC9.GPIOParameters=GPIO_Label
PC9.GPIO_Label=QSPI_D0 [N25Q128A13EF840E_DQ0]
PC9.Mode=Single Bank 1
PC9.Signal=QUADSPI_BK1_IO0
PD0.GPIOParameters=GPIO_Label
PD0.GPIO_Label=FMC_D2 [MT48LC4M32B2B5-6A_DQ2]
PD0.Signal=FMC_D2_DA2
PD1.GPIOParameters=GPIO_Label
PD1.GPIO_Label=FMC_D3 [MT48LC4M32B2B5-6A_DQ3]
PD1.Signal=FMC_D3_DA3
PD10.GPIOParameters=GPIO_Label
PD10.GPIO_Label=FMC_D15 [MT48LC4M32B2B5-6A_DQ15]
PD10.Signal=FMC_D15_DA15
PD11.GPIOParameters=GPIO_Label
PD11.GPIO_Label=SPDIF_TX [TP20]
PD11.Signal=SAI2_SD_A
PD12.GPIOParameters=GPIO_Label
PD12.GPIO_Label=AUDIO_SCL [WM8994ECS/R_SCLK]
PD12.Signal=I2C4_SCL
PD13.GPIOParameters=GPIO_Label
PD13.GPIO_Label=QSPI_D3 [N25Q128A13EF840E_DQ3]
PD13.Mode=Single Bank 1
PD13.Signal=QUADSPI_BK1_IO3
PD14.GPIOParameters=GPIO_Label
PD14.GPIO_Label=FMC_D0 [MT48LC4M32B2B5-6A_DQ0]
PD14.Signal=FMC_D0_DA0
PD15.GPIOParameters=GPIO_Label
PD15.GPIO_Label=FMC_D1 [MT48LC4M32B2B5-6A_DQ1]
PD15.Signal=FMC_D1_DA1
PD2.GPIOParameters=GPIO_Label
PD2.GPIO_Label=WIFI_TX
PD2.Signal=UART5_RX
PD3.GPIOParameters=GPIO_Label
PD3.GPIO_Label=DFSDM_CKOUT [TP102]
PD3.Signal=S_CKOUTDFSDM1
PD4.GPIOParameters=GPIO_Label
PD4.GPIO_Label=OTG_FS_OverCurrent [STMPS2141STR_Fault]
PD4.Signal=GPIO_Input
PD5.GPIOParameters=GPIO_Label
PD5.GPIO_Label=RMII_RXER[LAN8742A-CZ-TR_RXERR]
PD5.Signal=GPIO_Input
PD6.GPIOParameters=GPIO_Label
PD6.GPIO_Label=uSD_CLK
PD6.Signal=SDMMC2_CK
PD7.GPIOParameters=GPIO_Label
PD7.GPIO_Label=uSD_CMD
PD7.Signal=SDMMC2_CMD
PD8.GPIOParameters=GPIO_Label
PD8.GPIO_Label=FMC_D13 [MT48LC4M32B2B5-6A_DQ13]
PD8.Signal=FMC_D13_DA13
PD9.GPIOParameters=GPIO_Label
PD9.GPIO_Label=FMC_D14 [MT48LC4M32B2B5-6A_DQ14]
PD9.Signal=FMC_D14_DA14
PE0.GPIOParameters=GPIO_Label
PE0.GPIO_Label=FMC_NBL0 [MT48LC4M32B2B5-6A_DQM0]
PE0.Signal=FMC_NBL0
PE1.GPIOParameters=GPIO_Label
PE1.GPIO_Label=FMC_NBL1 [MT48LC4M32B2B5-6A_DQM1]
PE1.Signal=FMC_NBL1
PE10.GPIOParameters=GPIO_Label
PE10.GPIO_Label=FMC_D7 [MT48LC4M32B2B5-6A_DQ7]
PE10.Signal=FMC_D7_DA7
PE11.GPIOParameters=GPIO_Label
PE11.GPIO_Label=FMC_D8 [MT48LC4M32B2B5-6A_DQ8]
PE11.Signal=FMC_D8_DA8
PE12.GPIOParameters=GPIO_Label
PE12.GPIO_Label=FMC_D9 [MT48LC4M32B2B5-6A_DQ9]
PE12.Signal=FMC_D9_DA9
PE13.GPIOParameters=GPIO_Label
PE13.GPIO_Label=FMC_D10 [MT48LC4M32B2B5-6A_DQ10]
PE13.Signal=FMC_D10_DA10
PE14.GPIOParameters=GPIO_Label
PE14.GPIO_Label=FMC_D11 [MT48LC4M32B2B5-6A_DQ11]
PE14.Signal=FMC_D11_DA11
PE15.GPIOParameters=GPIO_Label
PE15.GPIO_Label=FMC_D12 [MT48LC4M32B2B5-6A_DQ12]
PE15.Signal=FMC_D12_DA12
PE2.GPIOParameters=GPIO_Label
PE2.GPIO_Label=QSPI_D2 [N25Q128A13EF840E_DQ2]
PE2.Mode=Single Bank 1
PE2.Signal=QUADSPI_BK1_IO2
PE3.GPIOParameters=GPIO_Label
PE3.GPIO_Label=SAI1_SDB [WM8994ECS/R_ADCDAT1]
PE3.Signal=SAI1_SD_B
PE4.GPIOParameters=GPIO_Label
PE4.GPIO_Label=SAI1_FSA [WM8994ECS/R_LRCLK1]
PE4.Signal=SAI1_FS_A
PE5.GPIOParameters=GPIO_Label
PE5.GPIO_Label=SAI1_SCKA [WM8994ECS/R_BCLK1]
PE5.Signal=SAI1_SCK_A
PE6.GPIOParameters=GPIO_Label
PE6.GPIO_Label=SAI1_SDA [WM8994ECS/R_DACDAT1]
PE6.Signal=SAI1_SD_A
PE7.GPIOParameters=GPIO_Label
PE7.GPIO_Label=FMC_D4 [MT48LC4M32B2B5-6A_DQ4]
PE7.Signal=FMC_D4_DA4
PE8.GPIOParameters=GPIO_Label
PE8.GPIO_Label=FMC_D5 [MT48LC4M32B2B5-6A_DQ5]
PE8.Signal=FMC_D5_DA5
PE9.GPIOParameters=GPIO_Label
PE9.GPIO_Label=FMC_D6 [MT48LC4M32B2B5-6A_DQ6]
PE9.Signal=FMC_D6_DA6
PF0.GPIOParameters=GPIO_Label
PF0.GPIO_Label=FMC_A0 [MT48LC4M32B2B5-6A_A0]
PF0.Signal=FMC_A0
PF1.GPIOParameters=GPIO_Label
PF1.GPIO_Label=FMC_A1 [MT48LC4M32B2B5-6A_A1]
PF1.Signal=FMC_A1
PF10.GPIOParameters=GPIO_PuPd,GPIO_Label,GPIO_Mode
PF10.GPIO_Label=ARDUINO A1
PF10.GPIO_Mode=GPIO_MODE_ANALOG
PF10.GPIO_PuPd=GPIO_NOPULL
PF10.Signal=ADC3_IN8
PF11.GPIOParameters=GPIO_Label
PF11.GPIO_Label=FMC_SDNRAS [MT48LC4M32B2B5-6A_RAS]
PF11.Signal=FMC_SDNRAS
PF12.GPIOParameters=GPIO_Label

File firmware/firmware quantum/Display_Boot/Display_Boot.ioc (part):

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Mcu.Name=STM32F469NIHx
Mcu.Package=TFBGA216
Mcu.UserName=STM32F469NIHx
PA0/WKUP.GPIOParameters=GPIO_Label
PA0/WKUP.GPIO_Label=WAKEUP [B2]
PA0/WKUP.Mode=SYS_WakeUp0
PA0/WKUP.Signal=SYS_WKUP
PA10.GPIOParameters=GPIO_Speed,GPIO_PuPd,GPIO_Label,GPIO_Mode
PA10.GPIO_Label=USB_FS1_ID
PA10.GPIO_Mode=GPIO_MODE_AF_PP
PA10.GPIO_PuPd=GPIO_NOPULL
PA10.GPIO_Speed=GPIO_SPEED_FREQ_VERY_HIGH
PA10.Signal=USB_OTG_FS_ID
PA11.GPIOParameters=GPIO_Speed,GPIO_PuPd,GPIO_Label,GPIO_Mode
PA11.GPIO_Label=USB_FS1_N
PA11.GPIO_Mode=GPIO_MODE_AF_PP
PA11.GPIO_PuPd=GPIO_NOPULL
PA11.GPIO_Speed=GPIO_SPEED_FREQ_VERY_HIGH
PA11.Signal=USB_OTG_FS_DM
PA12.GPIOParameters=GPIO_Speed,GPIO_PuPd,GPIO_Label,GPIO_Mode
PA12.GPIO_Label=USB_FS1_P
PA12.GPIO_Mode=GPIO_MODE_AF_PP
PA12.GPIO_PuPd=GPIO_NOPULL
PA12.GPIO_Speed=GPIO_SPEED_FREQ_VERY_HIGH
PA12.Signal=USB_OTG_FS_DP
PA13.GPIOParameters=GPIO_Label
PA13.GPIO_Label=SWDIO
PA13.Mode=Serial_Wire
PA13.Signal=SYS_JTMS-SWDIO
PA14.GPIOParameters=GPIO_Label
PA14.GPIO_Label=SWCLK
PA14.Mode=Serial_Wire
PA14.Signal=SYS_JTCK-SWCLK
PA3.GPIOParameters=GPIO_Speed,GPIO_PuPd,GPIO_Label,GPIO_ModeDefaultOutputPP
PA3.GPIO_Label=LCD_BL_CTRL [STLD40DPUR_EN]
PA3.GPIO_ModeDefaultOutputPP=GPIO_MODE_OUTPUT_PP
PA3.GPIO_PuPd=GPIO_NOPULL
PA3.GPIO_Speed=GPIO_SPEED_FREQ_LOW
PA3.Signal=GPIO_Output
PA9.GPIOParameters=GPIO_Speed,GPIO_PuPd,GPIO_Label,GPIO_Mode
PA9.GPIO_Label=VBUS_FS1
PA9.GPIO_Mode=GPIO_MODE_AF_PP
PA9.GPIO_PuPd=GPIO_NOPULL
PA9.GPIO_Speed=GPIO_SPEED_FREQ_VERY_HIGH
PA9.Signal=USB_OTG_FS_VBUS
PB0.GPIOParameters=GPIO_Speed,GPIO_PuPd,GPIO_Label,GPIO_ModeDefaultOutputPP
PB0.GPIO_Label=EXT_RESET
PB0.GPIO_ModeDefaultOutputPP=GPIO_MODE_OUTPUT_PP
PB0.GPIO_PuPd=GPIO_NOPULL
PB0.GPIO_Speed=GPIO_SPEED_FREQ_LOW
PB0.Signal=GPIO_Output
PB10.GPIOParameters=GPIO_Speed,GPIO_PuPd,GPIO_Label,GPIO_Mode
PB10.GPIO_Label=STLK_RX [STLINK V2-1_U2_RX]
PB10.GPIO_Mode=GPIO_MODE_AF_PP
PB10.GPIO_PuPd=GPIO_PULLUP
PB10.GPIO_Speed=GPIO_SPEED_FREQ_VERY_HIGH
PB10.Mode=Asynchronous
PB10.Signal=USART3_TX
PB11.GPIOParameters=GPIO_Speed,GPIO_PuPd,GPIO_Label,GPIO_Mode
PB11.GPIO_Label=STLK_TX [STLINK V2-1_U2_TX]
PB11.GPIO_Mode=GPIO_MODE_AF_PP
PB11.GPIO_PuPd=GPIO_PULLUP
PB11.GPIO_Speed=GPIO_SPEED_FREQ_VERY_HIGH
PB11.Mode=Asynchronous
PB11.Signal=USART3_RX
PB2/BOOT1.GPIOParameters=GPIO_Speed,GPIO_PuPd,GPIO_Label,GPIO_ModeDefaultOutputPP
PB2/BOOT1.GPIO_Label=OTG_FS1_PowerSwitchOn [STMPS2151STR_En]
PB2/BOOT1.GPIO_ModeDefaultOutputPP=GPIO_MODE_OUTPUT_PP
PB2/BOOT1.GPIO_PuPd=GPIO_NOPULL
PB2/BOOT1.GPIO_Speed=GPIO_SPEED_FREQ_LOW
PB2/BOOT1.Signal=GPIO_Output
PB3.GPIOParameters=GPIO_Speed,GPIO_PuPd,GPIO_Label,GPIO_Mode
PB3.GPIO_Label=I2S3_CK
PB3.GPIO_Mode=GPIO_MODE_AF_PP
PB3.GPIO_PuPd=GPIO_NOPULL
PB3.GPIO_Speed=GPIO_SPEED_FREQ_LOW
PB3.Signal=I2S3_CK
PB6.GPIOParameters=GPIO_Speed,GPIO_PuPd,GPIO_Label,GPIO_Mode
PB6.GPIO_Label=QSPI_BK1_NCS [N25Q128A13EF840F_S]
PB6.GPIO_Mode=GPIO_MODE_AF_PP
PB6.GPIO_PuPd=GPIO_NOPULL
PB6.GPIO_Speed=GPIO_SPEED_FREQ_VERY_HIGH
PB6.Signal=QUADSPI_BK1_NCS
PB7.GPIOParameters=GPIO_PuPd,GPIO_Label,GPIO_ModeDefaultEXTI
PB7.GPIO_Label=OTG_FS1_OverCurrent [STMPS2151STR_FAULT]
PB7.GPIO_ModeDefaultEXTI=GPIO_MODE_IT_RISING
PB7.GPIO_PuPd=GPIO_NOPULL
PB7.Signal=GPXTI7
PB8.GPIOParameters=GPIO_Speed,GPIO_PuPdOD,GPIO_Label,GPIO_Mode
PB8.GPIO_Label=I2C1_SCL
PB8.GPIO_Mode=GPIO_MODE_AF_OD
PB8.GPIO_PuPdOD=GPIO_PULLUP
PB8.GPIO_Speed=GPIO_SPEED_FREQ_VERY_HIGH
PB8.Signal=I2C1_SCL
PB9.GPIOParameters=GPIO_Speed,GPIO_PuPdOD,GPIO_Label,GPIO_Mode
PB9.GPIO_Label=I2C1_SDA
PB9.GPIO_Mode=GPIO_MODE_AF_OD
PB9.GPIO_PuPdOD=GPIO_PULLUP
PB9.GPIO_Speed=GPIO_SPEED_FREQ_VERY_HIGH
PB9.Signal=I2C1_SDA
PC0.GPIOParameters=GPIO_PuPd,GPIO_Speed_High_Default,GPIO_Label,GPIO_Mode
PC0.GPIO_Label=SDNWE [MT48LC4M32B2B5-6A_WE]
PC0.GPIO_Mode=GPIO_MODE_AF_PP
PC0.GPIO_PuPd=GPIO_NOPULL
PC0.GPIO_Speed_High_Default=GPIO_SPEED_FREQ_VERY_HIGH
PC0.Signal=FMC_SDNWE
PC10.GPIOParameters=GPIO_PuPd,GPIO_Speed_High_Default,GPIO_Label,GPIO_Mode
PC10.GPIO_Label=uSD_D2
PC10.GPIO_Mode=GPIO_MODE_AF_PP
PC10.GPIO_PuPd=GPIO_NOPULL
PC10.GPIO_Speed_High_Default=GPIO_SPEED_FREQ_VERY_HIGH
PC10.Signal=SDIO_D2
PC11.GPIOParameters=GPIO_PuPd,GPIO_Speed_High_Default,GPIO_Label,GPIO_Mode
PC11.GPIO_Label=uSD_D3
PC11.GPIO_Mode=GPIO_MODE_AF_PP
PC11.GPIO_PuPd=GPIO_NOPULL
PC11.GPIO_Speed_High_Default=GPIO_SPEED_FREQ_VERY_HIGH
PC11.Signal=SDIO_D3
PC12.GPIOParameters=GPIO_PuPd,GPIO_Speed_High_Default,GPIO_Label,GPIO_Mode
PC12.GPIO_Label=uSD_CLK
PC12.GPIO_Mode=GPIO_MODE_AF_PP
PC12.GPIO_PuPd=GPIO_NOPULL
PC12.GPIO_Speed_High_Default=GPIO_SPEED_FREQ_VERY_HIGH
PC12.Signal=SDIO_CK
PC14/OSC32_IN.Mode=LSE-External-Oscillator
PC14/OSC32_IN.Signal=RCC_OSC32_IN
PC15/OSC32_OUT.Mode=LSE-External-Oscillator
PC15/OSC32_OUT.Signal=RCC_OSC32_OUT
PC8.GPIOParameters=GPIO_PuPd,GPIO_Speed_High_Default,GPIO_Label,GPIO_Mode
PC8.GPIO_Label=uSD_D0
PC8.GPIO_Mode=GPIO_MODE_AF_PP
PC8.GPIO_PuPd=GPIO_NOPULL
PC8.GPIO_Speed_High_Default=GPIO_SPEED_FREQ_VERY_HIGH
PC8.Signal=SDIO_D0
PC9.GPIOParameters=GPIO_PuPd,GPIO_Speed_High_Default,GPIO_Label,GPIO_Mode
PC9.GPIO_Label=uSD_D1
PC9.GPIO_Mode=GPIO_MODE_AF_PP
PC9.GPIO_PuPd=GPIO_NOPULL
PC9.GPIO_Speed_High_Default=GPIO_SPEED_FREQ_VERY_HIGH
PC9.Signal=SDIO_D1
PD0.GPIOParameters=GPIO_PuPd,GPIO_Speed_High_Default,GPIO_Label,GPIO_Mode
PD0.GPIO_Label=D2
PD0.GPIO_Mode=GPIO_MODE_AF_PP
PD0.GPIO_PuPd=GPIO_NOPULL
PD0.GPIO_Speed_High_Default=GPIO_SPEED_FREQ_VERY_HIGH
PD0.Signal=FMC_D2_DA2
PD1.GPIOParameters=GPIO_PuPd,GPIO_Speed_High_Default,GPIO_Label,GPIO_Mode
PD1.GPIO_Label=D3
PD1.GPIO_Mode=GPIO_MODE_AF_PP
PD1.GPIO_PuPd=GPIO_NOPULL
PD1.GPIO_Speed_High_Default=GPIO_SPEED_FREQ_VERY_HIGH
PD1.Signal=FMC_D3_DA3
PD10.GPIOParameters=GPIO_PuPd,GPIO_Speed_High_Default,GPIO_Label,GPIO_Mode
PD10.GPIO_Label=D15
PD10.GPIO_Mode=GPIO_MODE_AF_PP
PD10.GPIO_PuPd=GPIO_NOPULL
PD10.GPIO_Speed_High_Default=GPIO_SPEED_FREQ_VERY_HIGH
PD10.Signal=FMC_D15_DA15
PD13.GPIOParameters=GPIO_ModeDefaultPP,GPIO_Speed,GPIO_PuPd,GPIO_Label
PD13.GPIO_Label=MIC_CK [MP34DT01TR_CLK]
PD13.GPIO_ModeDefaultPP=GPIO_MODE_AF_PP
PD13.GPIO_PuPd=GPIO_NOPULL
PD13.GPIO_Speed=GPIO_SPEED_FREQ_LOW
PD13.Signal=S_TIM4_CH2
PD14.GPIOParameters=GPIO_PuPd,GPIO_Speed_High_Default,GPIO_Label,GPIO_Mode
PD14.GPIO_Label=D0
PD14.GPIO_Mode=GPIO_MODE_AF_PP
PD14.GPIO_PuPd=GPIO_NOPULL
PD14.GPIO_Speed_High_Default=GPIO_SPEED_FREQ_VERY_HIGH
PD14.Signal=FMC_D0_DA0
PD15.GPIOParameters=GPIO_PuPd,GPIO_Speed_High_Default,GPIO_Label,GPIO_Mode
PD15.GPIO_Label=D1
PD15.GPIO_Mode=GPIO_MODE_AF_PP
PD15.GPIO_PuPd=GPIO_NOPULL
PD15.GPIO_Speed_High_Default=GPIO_SPEED_FREQ_VERY_HIGH
PD15.Signal=FMC_D1_DA1
PD2.GPIOParameters=GPIO_PuPd,GPIO_Speed_High_Default,GPIO_Label,GPIO_Mode
PD2.GPIO_Label=uSD_CMD
PD2.GPIO_Mode=GPIO_MODE_AF_PP
PD2.GPIO_PuPd=GPIO_NOPULL
PD2.GPIO_Speed_High_Default=GPIO_SPEED_FREQ_VERY_HIGH
PD2.Signal=SDIO_CMD
PD4.GPIOParameters=GPIO_Speed,GPIO_PuPd,GPIO_Label,GPIO_ModeDefaultOutputPP
PD4.GPIO_Label=LED2 [Orange]
PD4.GPIO_ModeDefaultOutputPP=GPIO_MODE_OUTPUT_OD
PD4.GPIO_PuPd=GPIO_NOPULL
PD4.GPIO_Speed=GPIO_SPEED_FREQ_LOW
PD4.Signal=GPIO_Output
PD5.GPIOParameters=GPIO_Speed,GPIO_PuPd,GPIO_Label,GPIO_ModeDefaultOutputPP
PD5.GPIO_Label=LED3 [Red]
PD5.GPIO_ModeDefaultOutputPP=GPIO_MODE_OUTPUT_OD
PD5.GPIO_PuPd=GPIO_NOPULL
PD5.GPIO_Speed=GPIO_SPEED_FREQ_LOW
PD5.Signal=GPIO_Output
PD6.GPIOParameters=GPIO_Speed,GPIO_PuPd,GPIO_Label,GPIO_Mode
PD6.GPIO_Label=MIC_DATA [MP34DT01TR_DOUT]
PD6.GPIO_Mode=GPIO_MODE_AF_PP
PD6.GPIO_PuPd=GPIO_NOPULL
PD6.GPIO_Speed=GPIO_SPEED_FREQ_LOW
PD6.Signal=SAI1_SD_A
PD8.GPIOParameters=GPIO_PuPd,GPIO_Speed_High_Default,GPIO_Label,GPIO_Mode
PD8.GPIO_Label=D13
PD8.GPIO_Mode=GPIO_MODE_AF_PP
PD8.GPIO_PuPd=GPIO_NOPULL
PD8.GPIO_Speed_High_Default=GPIO_SPEED_FREQ_VERY_HIGH
PD8.Signal=FMC_D13_DA13
PD9.GPIOParameters=GPIO_PuPd,GPIO_Speed_High_Default,GPIO_Label,GPIO_Mode
PD9.GPIO_Label=D14
PD9.GPIO_Mode=GPIO_MODE_AF_PP
PD9.GPIO_PuPd=GPIO_NOPULL
PD9.GPIO_Speed_High_Default=GPIO_SPEED_FREQ_VERY_HIGH
PD9.Signal=FMC_D14_DA14
PE0.GPIOParameters=GPIO_PuPd,GPIO_Speed_High_Default,GPIO_Label,GPIO_Mode
PE0.GPIO_Label=FMC_NBL0 [ MT48LC4M32B2B5-6A_DQM0]
PE0.GPIO_Mode=GPIO_MODE_AF_PP
PE0.GPIO_PuPd=GPIO_NOPULL
PE0.GPIO_Speed_High_Default=GPIO_SPEED_FREQ_VERY_HIGH
PE0.Signal=FMC_NBL0
PE1.GPIOParameters=GPIO_PuPd,GPIO_Speed_High_Default,GPIO_Label,GPIO_Mode
PE1.GPIO_Label=FMC_NBL1 [ MT48LC4M32B2B5-6A_DQM1]
PE1.GPIO_Mode=GPIO_MODE_AF_PP
PE1.GPIO_PuPd=GPIO_NOPULL
PE1.GPIO_Speed_High_Default=GPIO_SPEED_FREQ_VERY_HIGH
PE1.Signal=FMC_NBL1
PE10.GPIOParameters=GPIO_PuPd,GPIO_Speed_High_Default,GPIO_Label,GPIO_Mode
PE10.GPIO_Label=D7
PE10.GPIO_Mode=GPIO_MODE_AF_PP
PE10.GPIO_PuPd=GPIO_NOPULL
PE10.GPIO_Speed_High_Default=GPIO_SPEED_FREQ_VERY_HIGH
PE10.Signal=FMC_D7_DA7
PE11.GPIOParameters=GPIO_PuPd,GPIO_Speed_High_Default,GPIO_Label,GPIO_Mode
PE11.GPIO_Label=D8
PE11.GPIO_Mode=GPIO_MODE_AF_PP
PE11.GPIO_PuPd=GPIO_NOPULL
PE11.GPIO_Speed_High_Default=GPIO_SPEED_FREQ_VERY_HIGH
PE11.Signal=FMC_D8_DA8
PE12.GPIOParameters=GPIO_PuPd,GPIO_Speed_High_Default,GPIO_Label,GPIO_Mode
PE12.GPIO_Label=D9
PE12.GPIO_Mode=GPIO_MODE_AF_PP
PE12.GPIO_PuPd=GPIO_NOPULL
